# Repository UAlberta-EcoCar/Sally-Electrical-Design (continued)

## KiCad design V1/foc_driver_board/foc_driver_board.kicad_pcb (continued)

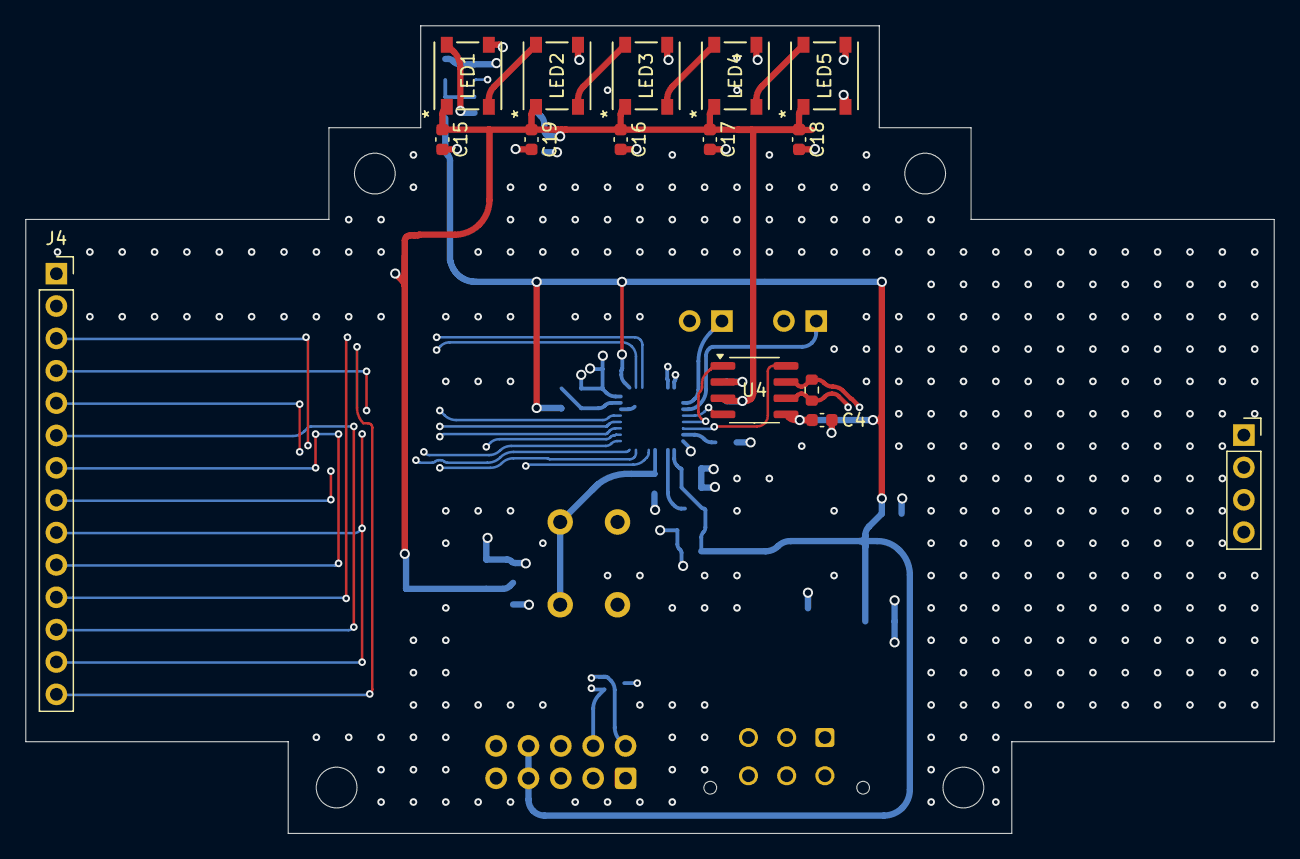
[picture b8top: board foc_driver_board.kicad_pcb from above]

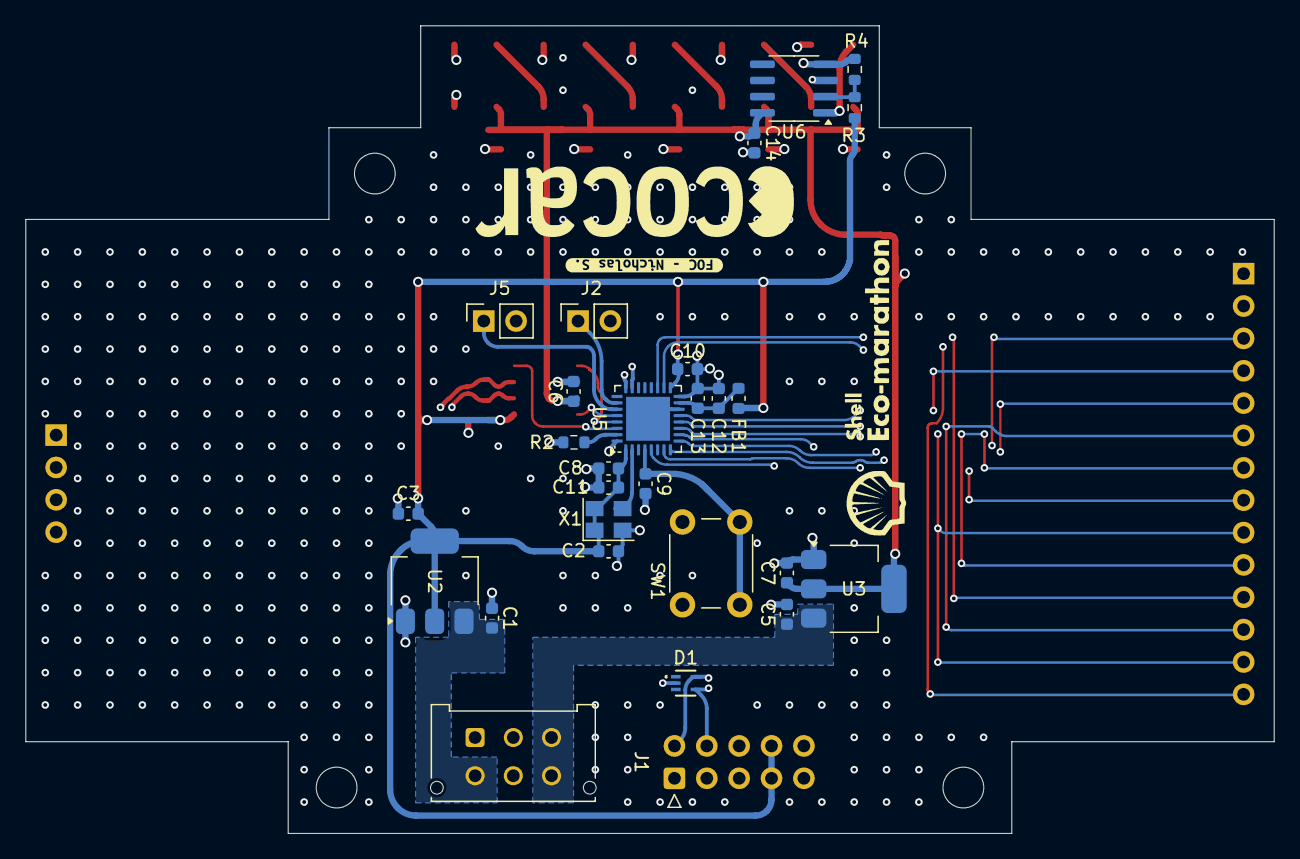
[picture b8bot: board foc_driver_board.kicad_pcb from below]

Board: 4 copper layers, 98.0 x 63.4 mm, 47 parts (29 on the bottom side), 34 nets.

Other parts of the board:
kibuzzard-678986CF: G***; kibuzzard-678986CF

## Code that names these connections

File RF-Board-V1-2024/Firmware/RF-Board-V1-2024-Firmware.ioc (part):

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Mcu.Name=STM32G484RETx
Mcu.Package=LQFP64
Mcu.UserName=STM32G484RETx
PA0.GPIOParameters=GPIO_Label
PA0.GPIO_Label=LED1
PA0.Signal=GPIO_Output
PA1.GPIOParameters=GPIO_Label
PA1.GPIO_Label=LED2
PA1.Signal=GPIO_Output
PA10.GPIOParameters=GPIO_Label
PA10.GPIO_Label=RST_24
PA10.Signal=GPIO_Output
PA11.Mode=Device
PA11.Signal=USB_DM
PA12.Mode=Device
PA12.Signal=USB_DP
PA13.GPIOParameters=GPIO_Label
PA13.GPIO_Label=SW_DIO
PA13.Mode=Serial_Wire
PA13.Signal=SYS_JTMS-SWDIO
PA14.GPIOParameters=GPIO_Label
PA14.GPIO_Label=SW_CLK
PA14.Mode=Serial_Wire
PA14.Signal=SYS_JTCK-SWCLK
PA2.GPIOParameters=GPIO_Label
PA2.GPIO_Label=LED3
PA2.Signal=GPIO_Output
PA3.GPIOParameters=GPIO_Label
PA3.GPIO_Label=LED4
PA3.Signal=GPIO_Output
PA4.GPIOParameters=GPIO_Label
PA4.GPIO_Label=SWT2
PA4.Signal=GPIO_Output
PA5.Mode=Full_Duplex_Master
PA5.Signal=SPI1_SCK
PA6.Mode=Full_Duplex_Master
PA6.Signal=SPI1_MISO
PA7.Mode=Full_Duplex_Master
PA7.Signal=SPI1_MOSI
PA8.Mode=I2C
PA8.Signal=I2C2_SDA
PA9.Mode=I2C
PA9.Signal=I2C2_SCL
PB0.GPIOParameters=GPIO_Label
PB0.GPIO_Label=NSS_24
PB0.Signal=GPIO_Output
PB1.GPIOParameters=GPIO_Label
PB1.GPIO_Label=RST_GNSS
PB1.Signal=GPIO_Output
PB10.GPIOParameters=GPIO_Label
PB10.GPIO_Label=DIO0_915
PB10.Signal=GPIO_Output
PB11.GPIOParameters=GPIO_Label
PB11.GPIO_Label=IMON
PB11.Signal=GPIO_Analog
PB12.Mode=FDCAN_Activate
PB12.Signal=FDCAN2_RX
PB13.Mode=FDCAN_Activate
PB13.Signal=FDCAN2_TX
PB14.Mode=Full_Duplex_Master
PB14.Signal=SPI2_MISO
PB15.Mode=Full_Duplex_Master
PB15.Signal=SPI2_MOSI
PB2.GPIOParameters=GPIO_Label
PB2.GPIO_Label=EXTINT_GNSS
PB2.Signal=GPIO_Output
PB3.GPIOParameters=GPIO_Label
PB3.GPIO_Label=RST_915
PB3.Signal=GPIO_Output
PB4.GPIOParameters=GPIO_Label
PB4.GPIO_Label=DIO5_915
PB4.Signal=GPIO_Output
PB5.GPIOParameters=GPIO_Label
PB5.GPIO_Label=DIO4_915
PB5.Signal=GPIO_Output
PB6.GPIOParameters=GPIO_Label
PB6.GPIO_Label=LED5
PB6.Signal=GPIO_Input
PB7.GPIOParameters=GPIO_Label
PB7.GPIO_Label=LED6
PB7.Signal=GPIO_Output
PB8-BOOT0.GPIOParameters=GPIO_Label
PB8-BOOT0.GPIO_Label=LED7
PB8-BOOT0.Signal=GPIO_Output
PB9.GPIOParameters=GPIO_Label
PB9.GPIO_Label=LED8
PB9.Signal=GPIO_Output
PC0.GPIOParameters=GPIO_Label
PC0.GPIO_Label=TXEN_24
PC0.Signal=GPIO_Output
PC1.GPIOParameters=GPIO_Label
PC1.GPIO_Label=RXEN_24
PC1.Signal=GPIO_Output
PC10.GPIOParameters=GPIO_Label
PC10.GPIO_Label=RST_868
PC10.Signal=GPIO_Output
PC11.GPIOParameters=GPIO_Label
PC11.GPIO_Label=DIO0_868
PC11.Signal=GPIO_Output
PC12.GPIOParameters=GPIO_Label
PC12.GPIO_Label=DIO4_868
PC12.Signal=GPIO_Output
PC13.GPIOParameters=GPIO_Label
PC13.GPIO_Label=BTN1
PC13.Signal=GPIO_Output
PC14-OSC32_IN.GPIOParameters=GPIO_Label
PC14-OSC32_IN.GPIO_Label=BTN2
PC14-OSC32_IN.Signal=GPIO_Output
PC2.GPIOParameters=GPIO_Label
PC2.GPIO_Label=SPI2_NSS
PC2.Signal=GPIO_Output
PC3.GPIOParameters=GPIO_Label
PC3.GPIO_Label=SWT1
PC3.Signal=GPIO_Output
PC4.GPIOParameters=GPIO_Label
PC4.GPIO_Label=NSS_915
PC4.Signal=GPIO_Output
PC5.GPIOParameters=GPIO_Label
PC5.GPIO_Label=NSS_868
PC5.Signal=GPIO_Output
PC6.GPIOParameters=GPIO_Label
PC6.GPIO_Label=DIO3_24
PC6.Signal=GPIO_Analog
PC7.GPIOParameters=GPIO_Label
PC7.GPIO_Label=DIO2_24
PC7.Signal=GPIO_Output
PC8.GPIOParameters=GPIO_Label
PC8.GPIO_Label=DIO1_24
PC8.Signal=GPIO_Output
PC9.GPIOParameters=GPIO_Label
PC9.GPIO_Label=BUSY_24
PC9.Signal=GPIO_Input
PD2.GPIOParameters=GPIO_Label
PD2.GPIO_Label=DIO5_868
PD2.Signal=GPIO_Input
PF0-OSC_IN.GPIOParameters=GPIO_Label
PF0-OSC_IN.GPIO_Label=XCLK
PF0-OSC_IN.Mode=HSE-External-Clock-Source
PF0-OSC_IN.Signal=RCC_OSC_IN
PF1-OSC_OUT.Mode=Full_Duplex_Master
PF1-OSC_OUT.Signal=SPI2_SCK
PG10-NRST.GPIOParameters=GPIO_Label
PG10-NRST.GPIO_Label=NOT_FAULT
PG10-NRST.Signal=GPIO_Input
RCC.HSE_VALUE=8000000
RCC.SYSCLKFreq_VALUE=150000000
RCC.SYSCLKSource=RCC_SYSCLKSOURCE_PLLCLK
board=custom

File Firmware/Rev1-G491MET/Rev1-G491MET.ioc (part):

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Mcu.Name=STM32G491M(C-E)Tx
Mcu.Package=LQFP80
Mcu.UserName=STM32G491METx
PA0.GPIOParameters=GPIO_Label
PA0.GPIO_Label=VOLT_MEAS_BUF_RES_LOW
PA0.Mode=IN1-Single-Ended
PA0.Signal=ADC1_IN1
PA1.GPIOParameters=GPIO_Label
PA1.GPIO_Label=MTR_RLY_RELAY_EN
PA1.Signal=GPIO_Output
PA10.GPIOParameters=GPIO_Label
PA10.GPIO_Label=GPBTN1
PA10.Signal=GPIO_Input
PA11.Mode=Device
PA11.Signal=USB_DM
PA12.Mode=Device
PA12.Signal=USB_DP
PA13.Mode=Serial_Wire
PA13.Signal=SYS_JTMS-SWDIO
PA14.Mode=Serial_Wire
PA14.Signal=SYS_JTCK-SWCLK
PA15.GPIOParameters=GPIO_Label
PA15.GPIO_Label=LED2R
PA15.Signal=GPIO_Output
PA2.GPIOParameters=GPIO_Label
PA2.GPIO_Label=MTR_RLY_COIL_CUR
PA2.Mode=IN3-Single-Ended
PA2.Signal=ADC1_IN3
PA3.GPIOParameters=GPIO_Label
PA3.GPIO_Label=MTR_RLY_STATUS
PA3.Signal=GPIO_Input
PA4.GPIOParameters=GPIO_Label
PA4.GPIO_Label=MTR_RLY_CUR_SENSE
PA4.Mode=IN17-Single-Ended
PA4.Signal=ADC2_IN17
PA5.GPIOParameters=GPIO_Label
PA5.GPIO_Label=RES_HIGH_RLY_RELAY_EN
PA5.Signal=GPIO_Output
PA6.GPIOParameters=GPIO_Label
PA6.GPIO_Label=RES_HIGH_RLY_COIL_CUR
PA6.Mode=IN3-Single-Ended
PA6.Signal=ADC2_IN3
PA7.GPIOParameters=GPIO_Label
PA7.GPIO_Label=RES_HIGH_RLY_STATUS
PA7.Signal=GPIO_Input
PA8.Mode=Clock-out
PA8.Signal=RCC_MCO
PB0.GPIOParameters=GPIO_Label
PB0.GPIO_Label=RES_LOW_RLY_COIL_CUR
PB0.Mode=IN15-Single-Ended
PB0.Signal=ADC1_IN15
PB1.GPIOParameters=GPIO_Label
PB1.GPIO_Label=RES_LOW_RLY_STATUS
PB1.Mode=IN1-Single-Ended
PB1.Signal=ADC3_IN1
PB12.GPIOParameters=GPIO_Label
PB12.GPIO_Label=SYS_7V_VOLT
PB12.Mode=IN11-Single-Ended
PB12.Signal=ADC1_IN11
PB13.GPIOParameters=GPIO_Label
PB13.GPIO_Label=SYS_12V_VOLT
PB13.Mode=IN5-Single-Ended
PB13.Signal=ADC3_IN5
PB14.GPIOParameters=GPIO_Label
PB14.GPIO_Label=SYS_12V_CUR
PB14.Mode=IN5-Single-Ended
PB14.Signal=ADC1_IN5
PB15.GPIOParameters=GPIO_Label
PB15.GPIO_Label=SYS_7V_CUR
PB15.Mode=IN15-Single-Ended
PB15.Signal=ADC2_IN15
PB2.GPIOParameters=GPIO_Label
PB2.GPIO_Label=RES_LOW_RLY_CUR_SENSE
PB2.Mode=IN12-Single-Ended
PB2.Signal=ADC2_IN12
PB5.GPIOParameters=GPIO_Label
PB5.GPIO_Label=GPBTN3
PB5.Signal=GPXTI5
PB6.GPIOParameters=GPIO_Label
PB6.GPIO_Label=GPBTN2
PB6.Signal=GPXTI6
PB8-BOOT0.GPIOParameters=GPIO_Label
PB8-BOOT0.GPIO_Label=BOOT0
PB8-BOOT0.Signal=GPIO_Input
PC0.GPIOParameters=GPIO_Label
PC0.GPIO_Label=VOLT_MEAS_BUF_FC_UP
PC0.Mode=IN6-Single-Ended
PC0.Signal=ADC1_IN6
PC1.GPIOParameters=GPIO_Label
PC1.GPIO_Label=VOLT_MEAS_BUF_FC_OUT
PC1.Mode=IN7-Single-Ended
PC1.Signal=ADC1_IN7
PC14-OSC32_IN.Signal=GPIO_Output
PC15-OSC32_OUT.Signal=GPIO_Output
PC2.GPIOParameters=GPIO_Label
PC2.GPIO_Label=VOLT_MEAS_BUF_CAP
PC2.Mode=IN8-Single-Ended
PC2.Signal=ADC1_IN8
PC3.GPIOParameters=GPIO_Label
PC3.GPIO_Label=VOLT_MEAS_BUF_RES_HIGH
PC3.Mode=IN9-Single-Ended
PC3.Signal=ADC1_IN9
PC4.GPIOParameters=GPIO_Label
PC4.GPIO_Label=RES_HIGH_RLY_CUR_SENSE
PC4.Mode=IN5-Single-Ended
PC4.Signal=ADC2_IN5
PC5.GPIOParameters=GPIO_Label
PC5.GPIO_Label=RES_LOW_RLY_RELAY_EN
PC5.Signal=GPIO_Output
PD0.Mode=FDCAN_Activate
PD0.Signal=FDCAN1_RX
PD1.Mode=FDCAN_Activate
PD1.Signal=FDCAN1_TX
PD10.GPIOParameters=GPIO_Label
PD10.GPIO_Label=FC_RLY_FC_CUR
PD10.Mode=IN7-Single-Ended
PD10.Signal=ADC3_IN7
PD9.GPIOParameters=GPIO_Label
PD9.GPIO_Label=FC_RLY_FC_EN
PD9.Signal=GPIO_Output
PE10.GPIOParameters=GPIO_Label
PE10.GPIO_Label=CAP_RLY_CUR_SENSE
PE10.Mode=IN14-Single-Ended
PE10.Signal=ADC3_IN14
PE11.GPIOParameters=GPIO_Label
PE11.GPIO_Label=TEMP_BOARD_VIN_DIODE
PE11.Mode=IN15-Single-Ended
PE11.Signal=ADC3_IN15
PE12.GPIOParameters=GPIO_Label
PE12.GPIO_Label=TEMP_BOARD_CENTER
PE12.Mode=IN16-Single-Ended
PE12.Signal=ADC3_IN16
PE13.GPIOParameters=GPIO_Label
PE13.GPIO_Label=VOLT_MEAS_BUF_MTR_OUT
PE13.Mode=IN3-Single-Ended
PE13.Signal=ADC3_IN3
PE14.GPIOParameters=GPIO_Label
PE14.GPIO_Label=LED1B
PE14.Signal=GPIO_Output
PE7.GPIOParameters=GPIO_Label
PE7.GPIO_Label=CAP_RLY_RELAY_EN
PE7.Signal=GPIO_Output
PE8.GPIOParameters=GPIO_Label
PE8.GPIO_Label=CAP_RLY_COIL_CUR
PE8.Mode=IN6-Single-Ended
PE8.Signal=ADC3_IN6
PE9.GPIOParameters=GPIO_Label
PE9.GPIO_Label=CAP_RLY_STATUS
PE9.Signal=GPIO_Input
PF0-OSC_IN.Mode=HSE-External-Clock-Source
PF0-OSC_IN.Signal=RCC_OSC_IN
PG10-NRST.GPIOParameters=GPIO_Label
PG10-NRST.GPIO_Label=NRST
PG10-NRST.Signal=GPIO_Input
RCC.HSE_VALUE=8000000
RCC.SYSCLKFreq_VALUE=16000000
board=custom

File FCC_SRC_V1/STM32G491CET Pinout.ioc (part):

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Mcu.Name=STM32G491C(C-E)Tx
Mcu.Package=LQFP48
Mcu.UserName=STM32G491CETx
PA0.GPIOParameters=GPIO_Label
PA0.GPIO_Label=EXTstop
PA0.Signal=GPXTI0
PA1.GPIOParameters=GPIO_Label
PA1.GPIO_Label=EXTstart
PA1.Signal=GPXTI1
PA10.GPIOParameters=GPIO_Label
PA10.GPIO_Label=TACH3
PA10.Signal=GPXTI10
PA11.Mode=Device
PA11.Signal=USB_DM
PA12.Mode=Device
PA12.Signal=USB_DP
PA13.Mode=Serial_Wire
PA13.Signal=SYS_JTMS-SWDIO
PA14.Mode=Serial_Wire
PA14.Signal=SYS_JTCK-SWCLK
PA15.GPIOParameters=GPIO_Speed,GPIO_Pu
PA15.GPIO_Pu=GPIO_NOPULL
PA15.GPIO_Speed=GPIO_SPEED_FREQ_VERY_HIGH
PA15.Mode=I2C
PA15.Signal=I2C1_SCL
PA2.GPIOParameters=GPIO_Label,GPIO_ModeDefaultEXTI
PA2.GPIO_Label=EncoderA
PA2.GPIO_ModeDefaultEXTI=GPIO_MODE_IT_RISING
PA2.Signal=GPXTI2
PA3.GPIOParameters=GPIO_Label
PA3.GPIO_Label=EncoderB
PA3.Signal=GPXTI3
PA4.GPIOParameters=GPIO_Label
PA4.GPIO_Label=EncoderPB
PA4.Signal=GPXTI4
PA5.GPIOParameters=GPIO_Label
PA5.GPIO_Label=AccINT1
PA5.Signal=GPXTI5
PA6.GPIOParameters=GPIO_Label
PA6.GPIO_Label=AccINT2
PA6.Signal=GPXTI6
PA7.GPIOParameters=GPIO_Label
PA7.GPIO_Label=TACH1
PA7.Signal=GPXTI7
PA8.Mode=Clock-out
PA8.Signal=RCC_MCO
PA9.GPIOParameters=GPIO_Label
PA9.GPIO_Label=TACH2
PA9.Signal=GPXTI9
PB0.GPIOParameters=GPIO_Label
PB0.GPIO_Label=PURGEvlve
PB0.Signal=GPIO_Output
PB1.GPIOParameters=GPIO_Label
PB1.GPIO_Label=SUPPLYvlve
PB1.Signal=GPIO_Output
PB10.GPIOParameters=GPIO_Label
PB10.GPIO_Label=LED4
PB10.Signal=GPIO_Output
PB11.GPIOParameters=GPIO_PuPd,GPIO_Label
PB11.GPIO_Label=CAN_STBY
PB11.GPIO_PuPd=GPIO_PULLDOWN
PB11.Signal=GPIO_Output
PB12.GPIOParameters=GPIO_Label
PB12.GPIO_Label=TACH4
PB12.Signal=GPXTI12
PB13.GPIOParameters=GPIO_Speed
PB13.GPIO_Speed=GPIO_SPEED_FREQ_HIGH
PB13.Mode=FDCAN_Activate
PB13.Signal=FDCAN2_TX
PB14.GPIOParameters=GPIO_Label
PB14.GPIO_Label=PURGEDUR
PB14.Mode=IN5-Single-Ended
PB14.Signal=ADC1_IN5
PB15.GPIOParameters=GPIO_Label
PB15.GPIO_Label=PURGEDEL
PB15.Mode=IN15-Single-Ended
PB15.Signal=ADC2_IN15
PB2.GPIOParameters=GPIO_Label
PB2.GPIO_Label=LED1
PB2.Signal=GPIO_Output
PB3.GPIOParameters=GPIO_Label
PB3.GPIO_Label=pwm1
PB3.Signal=S_TIM2_CH2
PB4.GPIOParameters=GPIO_Label
PB4.GPIO_Label=pwm2
PB4.Signal=S_TIM3_CH1
PB5.GPIOParameters=GPIO_Speed,GPIO_PuPd
PB5.GPIO_PuPd=GPIO_PULLUP
PB5.GPIO_Speed=GPIO_SPEED_FREQ_HIGH
PB5.Mode=FDCAN_Activate
PB5.Signal=FDCAN2_RX
PB6.GPIOParameters=GPIO_Label
PB6.GPIO_Label=LED2
PB6.Signal=GPIO_Output
PB7.GPIOParameters=GPIO_Speed,GPIO_Pu
PB7.GPIO_Pu=GPIO_NOPULL
PB7.GPIO_Speed=GPIO_SPEED_FREQ_VERY_HIGH
PB7.Mode=I2C
PB7.Signal=I2C1_SDA
PB8-BOOT0.GPIOParameters=GPIO_PuPd,GPIO_Label
PB8-BOOT0.GPIO_Label=FCPurge
PB8-BOOT0.GPIO_PuPd=GPIO_PULLUP
PB8-BOOT0.Signal=GPXTI8
PB9.GPIOParameters=GPIO_Label
PB9.GPIO_Label=LED3
PB9.Signal=GPIO_Output
PC13.Signal=GPIO_Analog
PC14-OSC32_IN.GPIOParameters=GPIO_PuPd,GPIO_Label,GPIO_ModeDefaultEXTI
PC14-OSC32_IN.GPIO_Label=BTN1
PC14-OSC32_IN.GPIO_ModeDefaultEXTI=GPIO_MODE_IT_RISING
PC14-OSC32_IN.GPIO_PuPd=GPIO_PULLUP
PC14-OSC32_IN.Signal=GPXTI14
PC15-OSC32_OUT.GPIOParameters=GPIO_PuPd,GPIO_Label,GPIO_ModeDefaultEXTI
PC15-OSC32_OUT.GPIO_Label=BTN2
PC15-OSC32_OUT.GPIO_ModeDefaultEXTI=GPIO_MODE_IT_RISING
PC15-OSC32_OUT.GPIO_PuPd=GPIO_PULLUP
PC15-OSC32_OUT.Signal=GPXTI15
PF0-OSC_IN.Mode=HSE-External-Clock-Source
PF0-OSC_IN.Signal=RCC_OSC_IN
PF1-OSC_OUT.Signal=GPIO_Analog
RCC.HSE_VALUE=8000000
RCC.SYSCLKFreq_VALUE=170000000
RCC.SYSCLKSource=RCC_SYSCLKSOURCE_PLLCLK
board=custom

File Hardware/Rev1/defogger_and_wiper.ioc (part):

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Mcu.Name=STM32G491K(C-E)Ux
Mcu.Package=UFQFPN32
Mcu.UserName=STM32G491KEUx
PA1.GPIOParameters=GPIO_Label
PA1.GPIO_Label=CAN_SYNC
PA1.Signal=GPIO_Output
PA10.GPIOParameters=GPIO_Label
PA10.GPIO_Label=NSTBY
PA10.Signal=GPIO_Output
PA11.Mode=Device
PA11.Signal=USB_DM
PA12.Mode=Device
PA12.Signal=USB_DP
PA13.Signal=SYS_JTMS-SWDIO
PA14.Signal=SYS_JTCK-SWCLK
PA3.GPIOParameters=GPIO_Label
PA3.GPIO_Label=ADC_VA
PA3.Mode=IN4-Single-Ended
PA3.Signal=ADC1_IN4
PA6.GPIOParameters=GPIO_Label
PA6.GPIO_Label=PWM1A
PA6.Signal=S_TIM16_CH1
PA7.GPIOParameters=GPIO_Label
PA7.GPIO_Label=PWM1B
PA7.Signal=S_TIM17_CH1
PA8.GPIOParameters=GPIO_Label
PA8.GPIO_Label=PHA
PA8.Signal=GPIO_Output
PA9.GPIOParameters=GPIO_Label
PA9.GPIO_Label=PHB
PA9.Signal=GPIO_Output
PB0.GPIOParameters=GPIO_Label
PB0.GPIO_Label=ADC_VB
PB0.Mode=IN15-Single-Ended
PB0.Signal=ADC1_IN15
PB3.GPIOParameters=GPIO_Label
PB3.GPIO_Label=ENB
PB3.Signal=GPIO_Output
PB4.GPIOParameters=GPIO_Label
PB4.GPIO_Label=ENA
PB4.Signal=GPIO_Output
PB5.Mode=FDCAN_Activate
PB5.Signal=FDCAN2_RX
PB6.Mode=FDCAN_Activate
PB6.Signal=FDCAN2_TX
PB7.GPIOParameters=GPIO_Label
PB7.GPIO_Label=OLED_SDA
PB7.Mode=I2C
PB7.Signal=I2C1_SDA
PB8-BOOT0.GPIOParameters=GPIO_Label
PB8-BOOT0.GPIO_Label=OLED_SCL
PB8-BOOT0.Mode=I2C
PB8-BOOT0.Signal=I2C1_SCL
PF0-OSC_IN.Mode=HSE-External-Oscillator
PF0-OSC_IN.Signal=RCC_OSC_IN
PF1-OSC_OUT.Mode=HSE-External-Oscillator
PF1-OSC_OUT.Signal=RCC_OSC_OUT
RCC.HSE_VALUE=8000000
RCC.SYSCLKFreq_VALUE=16000000
board=custom

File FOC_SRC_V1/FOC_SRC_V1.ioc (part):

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Mcu.Name=STM32G491K(C-E)Ux
Mcu.Package=UFQFPN32
Mcu.UserName=STM32G491KEUx
PA0.Signal=S_TIM2_CH1
PA13.Mode=Serial_Wire
PA13.Signal=SYS_JTMS-SWDIO
PA14.Mode=Serial_Wire
PA14.Signal=SYS_JTCK-SWCLK
PA2.GPIOParameters=GPIO_Label
PA2.GPIO_Label=LCD_BRIGHT
PA2.Signal=GPIO_Analog
PA3.GPIOParameters=GPIO_Label
PA3.GPIO_Label=LCD_DCRS
PA3.Signal=GPIO_Analog
PA4.GPIOParameters=GPIO_Label
PA4.GPIO_Label=LCD_CS
PA4.Signal=GPIO_Output
PA5.Mode=Full_Duplex_Master
PA5.Signal=SPI1_SCK
PA6.Mode=Full_Duplex_Master
PA6.Signal=SPI1_MISO
PA7.Mode=Full_Duplex_Master
PA7.Signal=SPI1_MOSI
PA8.GPIOParameters=GPIO_Label
PA8.GPIO_Label=T_IRQ
PA8.Signal=GPXTI8
PA9.GPIOParameters=GPIO_Label
PA9.GPIO_Label=T_CS
PA9.Signal=GPIO_Output
PB0.GPIOParameters=GPIO_Label
PB0.GPIO_Label=LCD_RESET
PB0.Signal=GPIO_Output
PB3.GPIOParameters=GPIO_PuPd,GPIO_Label,GPIO_ModeDefaultEXTI
PB3.GPIO_Label=BUTTON_1
PB3.GPIO_ModeDefaultEXTI=GPIO_MODE_IT_FALLING
PB3.GPIO_PuPd=GPIO_PULLUP
PB3.Signal=GPXTI3
PB4.GPIOParameters=GPIO_PuPd,GPIO_Label,GPIO_ModeDefaultEXTI
PB4.GPIO_Label=BUTTON_2
PB4.GPIO_ModeDefaultEXTI=GPIO_MODE_IT_FALLING
PB4.GPIO_PuPd=GPIO_PULLUP
PB4.Signal=GPXTI4
PB5.GPIOParameters=GPIO_Speed,GPIO_PuPd,GPIO_Mode
PB5.GPIO_Mode=GPIO_MODE_AF_PP
PB5.GPIO_PuPd=GPIO_PULLUP
PB5.GPIO_Speed=GPIO_SPEED_FREQ_LOW
PB5.Mode=FDCAN_Activate
PB5.Signal=FDCAN2_RX
PB6.GPIOParameters=GPIO_Speed,GPIO_FM6,GPIO_PuPd,GPIO_Mode
PB6.GPIO_FM6=__NULL
PB6.GPIO_Mode=GPIO_MODE_AF_PP
PB6.GPIO_PuPd=GPIO_NOPULL
PB6.GPIO_Speed=GPIO_SPEED_FREQ_LOW
PB6.Mode=FDCAN_Activate
PB6.Signal=FDCAN2_TX
PB7.GPIOParameters=GPIO_PuPd,GPIO_Label
PB7.GPIO_Label=CAN_STBY
PB7.GPIO_PuPd=GPIO_NOPULL
PB7.Signal=GPIO_Output
PF0-OSC_IN.Mode=HSE-External-Clock-Source
PF0-OSC_IN.Signal=RCC_OSC_IN
RCC.HSE_VALUE=8000000
RCC.SYSCLKFreq_VALUE=160000000
RCC.SYSCLKSource=RCC_SYSCLKSOURCE_PLLCLK
board=custom

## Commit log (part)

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2025-02-17 reworked the power layout of boostv2
2025-02-17 pushing submodule changes
2025-02-17 did a decent amount of rework on the code so far
2025-02-17 updated layout again
2025-02-17 did some work
2025-02-18 lots of work
2025-02-19 Added stuff
2025-02-20 end-of-day update
2025-02-21 did work on h2 board
2025-02-21 New file for testing
2025-02-21 My test worked
2025-02-21 clear layout DRC
2025-02-21 layout complete
2025-02-21 Did some finishing touches on the boost v2, zeesh plz review
2025-02-21 Cleaned up the last few errors
2025-02-21 Fixed last remaining errors
2025-02-22 generated gerbers
2025-02-22 Redid folder
2025-02-22 H2Board Gerber generated
2025-02-22 MoSen gerber generated
2025-02-22 zip gerbers
2025-02-22 what
2025-02-23 did lots of work on the code side of things, test out new usb logging feature!
2025-02-24 code work
2025-02-24 little changes
2025-02-25 usb twerks
2025-02-26 can works!
2025-02-27 yeet
2025-02-27 usb is all working properly, i2c now has semaphore protection for screen and adc. Still need i2c implementation with the accelerometer. Use a transfer function to calculate velocity if possible.
2025-02-28 test
2025-02-28 Updated and added threads
2025-02-28 removed tinyusb
2025-03-01 minor changes
2025-03-02 updatye
2025-03-02 pid loop
2025-03-02 Add LCD Test Project
2025-03-07 Added most firm
2025-03-07 fuck
2025-03-08 ADC Added
2025-03-08 ioc can update
2025-03-08 task created
2025-03-09 work from today
2025-03-09 added ws2812 drivers, completely untested
2025-03-09 programs, dma seems to work, leds are on backwards
2025-03-09 Fixed wiring error
2025-03-10 made a script and added Debug to ignore
2025-03-11 Revert "Adding ignore file for KiCad temp files"
    This reverts commit 9e36cc317fc3365b14d2634522c1efa00c27cff1.
2025-03-11 code update
2025-03-12 aslkdjfalksdf
2025-03-12 gitignore
2025-03-12 kicad 9!
2025-03-13 useful script
2025-03-13 OLED
2025-03-15 Added ws2812 drivers, still buggy though
2025-03-15 removed lock file
2025-03-15 commit stash
2025-03-15 Got rf working
2025-03-15 Fixed kmergre to abis code base
2025-03-16 work session 15 mar
2025-03-16 stuff
2025-03-16 Fix buggy WS2812 LEDs
2025-03-16 New folder for batt board with temperature sensors working
2025-03-21 Added ADC conversions
2025-03-21 checking to make sure can sync works
2025-03-22 Add 2 LED states
2025-03-22 Add brightness animation
2025-03-23 Add LED animations for relay states (untested)
2025-03-29 Fix CanBus communication
2025-03-29 Create GPIO Interrupt Handler
2025-03-29 Add CAN stuff
2025-03-29 Add button 1 handling
2025-03-29 Update CAN header
2025-03-30 Add button handling
2025-04-01 force purge
2025-04-04 PURGE CYCLE
2025-04-04 new thermistor curve for testing purposes
2025-04-04 push
2025-04-05 OLED change
2025-04-07 swag
2025-05-11 Revert "A:"
    This reverts commit 91a5f5b7d847f79503e2fb12a5b0a69ff4a4e457.
2025-06-25 Added programming template for onboarding
2025-06-28 added things
2025-07-17 Init
2025-07-17 Hardware
2025-07-19 Rev 2
2025-07-21 First commit.
2025-07-26 proj init
2025-07-26 added suspension height and brake temp sch sheets
2025-07-27 added temp IR sensor
2025-08-09 Rev 1.3
2025-08-12 First KiCAD commit
2025-08-12 removed unecessary files
2025-08-12 Added .gitignore
2025-08-12 New changes to power delivery on schematic
2025-08-12 New file added to .gitignnore and removed a file from repo
2025-08-13 Added HSE Oscillator to Schematic
2025-08-13 Added file to .gitignore
2025-08-13 Finished Setting up the MCU
2025-08-22 Adding Hierachiral Schematics
2025-08-23 Added a new IC and put files into folders
2025-08-25 I changes some of the MCU parts and Power
2025-08-30 Huzaifa Join
2025-09-04 Completed Main Board power Section
2025-09-06 Rearranged files for a consistant format post comp
2025-09-06 Upgraded IOC to newest version 1.6.1
2025-09-06 Fixed submodule issue and changed the oled status display to include all states
2025-09-07 Removed .DS_Store file
2025-09-08 New Efuse and Nice Power Schematic
2025-09-08 Backlink to CADLAB.io has been added.
2025-09-08 Edited power sheet schematic
2025-09-10 Nothing new
2025-09-10 made some notes
2025-09-10 Switched MCU to have more pins (same family as before). Added IDC pins, and control board PCB
2025-09-13 Microprocessor Revison
2025-09-13 Rev1
2025-09-14 New dip switches for the driving modes
2025-09-15 Added powerpole
2025-09-20 Pushed test firmware for light board
2025-09-23 new sheets and edits
2025-09-27 Completed eFuse and Starting on Layout
2025-10-04 updated current limiter design and added pull-ups to OLED screen
2025-10-04 New MCU, Configured Pins, Attached some footprints
2025-10-11 Updated schematics
2025-10-18 Added potentiometer to buck converter and New schematic for MOSFET boards
2025-10-23 Done MCU Waiting review
2025-10-23 Ideal didode controller
2025-10-25 Revision before Hall Effect Sensor
2025-10-25 Comlpeted Schematic(needs some small component values only)
2025-10-25 component placement
2025-10-29 Schematic revision for review
2025-10-30 restored power sheet, ready for review
2025-11-01 boostv3
2025-11-02 first review done
2025-11-02 Final revision
2025-11-03 added fiducials
2025-11-12 Saving Progress
2025-11-15 routing
2025-11-16 Saving Progress (Changed eFuse and comments)
2025-11-16 Schematic for revision
2025-11-22 added the voltage rails
2025-11-27 finished routing need ERC
2025-11-29 Added JST Connector, with footprint and finished LEDs
2025-11-30 finished layout for review
2025-12-16 Did Some Schematic Clean up and Vibe coded a imgui ui renderer in python with hot reload
2025-12-23 Schematic for review
2025-12-26 Almost completed MOSFET board component selection
2025-12-27 updated schematic 12-27-2025
2025-12-28 All footprints assigned and new schematic changes
2025-12-28 Clearing up electrical rule errors
2025-12-28 Schematic complete and ready for review
2025-12-29 beginning of the layout
2025-12-31 Replaced 12V-5V LDO with buck
2026-01-03 Changed layout worksesh Jan 3rd 2026
2026-01-06 Almost done
2026-01-06 Only GND a plane and GND Pours left
2026-01-08 Main Board Completed
2026-01-11 updated the power lines
2026-01-11 updated schem and pcb
2026-01-12 latest version ready for review
2026-01-14 final edits
2026-01-16 changed board appearance
2026-01-17 used zones to route power
2026-01-18 clean up
2026-01-18 MOSFET Board(s) Ready For Review
2026-01-19 changed to buses for 3v3 and did DRC
2026-01-29 Schematic Complete: New/Better Bucks
2026-02-02 Ready to order
2026-02-08 Last b4 buy
2026-02-09 added panel files
2026-02-09 Poured gnd on all layers and changed clearance to 0.18
2026-02-10 Updated trace thickness and capacitor positions
2026-02-14 added rbt
2026-02-15 Added missing break in app_freertos inturrupt handler for GPIO EXTI, aparently fan toggle would also purge????
2026-02-16 Update documentation
2026-02-16 Remove debug files from git
2026-02-16 connectors changed, routing to do
2026-02-24 Layout Placement Complete, Routing Remains
2026-02-25 Most Of Power Is Connected
2026-02-25 All Digital Circuitry Connected
2026-02-25 Mother Board Complete. Only BOM and small silkscreen adjustments needed, other than that the board system is complete
2026-02-25 Completed Load-Bank Automation Project Files V1.0
2026-02-25 Complete Load-Bank Automation Project V1.0 With Production Files
2026-02-26 create gerber copy for fabrication
2026-02-28 begin standardizing R values
2026-02-28 Moved led traces to internal layers
2026-03-28 updated layout
2026-03-29 Update kicad version
2026-03-29 Uncomment purge valve code
2026-03-31 Added subs for comps
2026-04-03 Fixed the issue and found that relay diode and foot print were wrong see schematic for spdt for details rev 1.
2026-04-04 added RGB Leds
2026-04-04 Add gitignore file for STM32 project
2026-04-27 figured out relay current monitoring is wrong
2026-04-28 Tested All relays and tested ideal diode, both work
2026-05-02 Convert firmware to use CMake
2026-05-02 Fix CMake errors
2026-05-02 Fix uncommented code
2026-05-02 2026-05-02 changes
2026-05-02 Add CAN receive functionality
2026-05-09 Fix git submodules not working
2026-05-16 add new CAN messages to receive functions
2026-05-27 LEDs light pannels no through holes
2026-05-30 Changed the connector
2026-06-03 MOSFET Board Layout is good
2026-06-03 Ready for order
2026-06-06 Finished all revisions
2026-06-06 MOSFET boards ready to be ordered
2026-06-12 Updated PCD and Schematic
2026-06-13 Added pull downs to enab;le and stays low for startup on relays, also confirmed with new 491 firmware
2026-06-27 fix RF DESIGN PCB
